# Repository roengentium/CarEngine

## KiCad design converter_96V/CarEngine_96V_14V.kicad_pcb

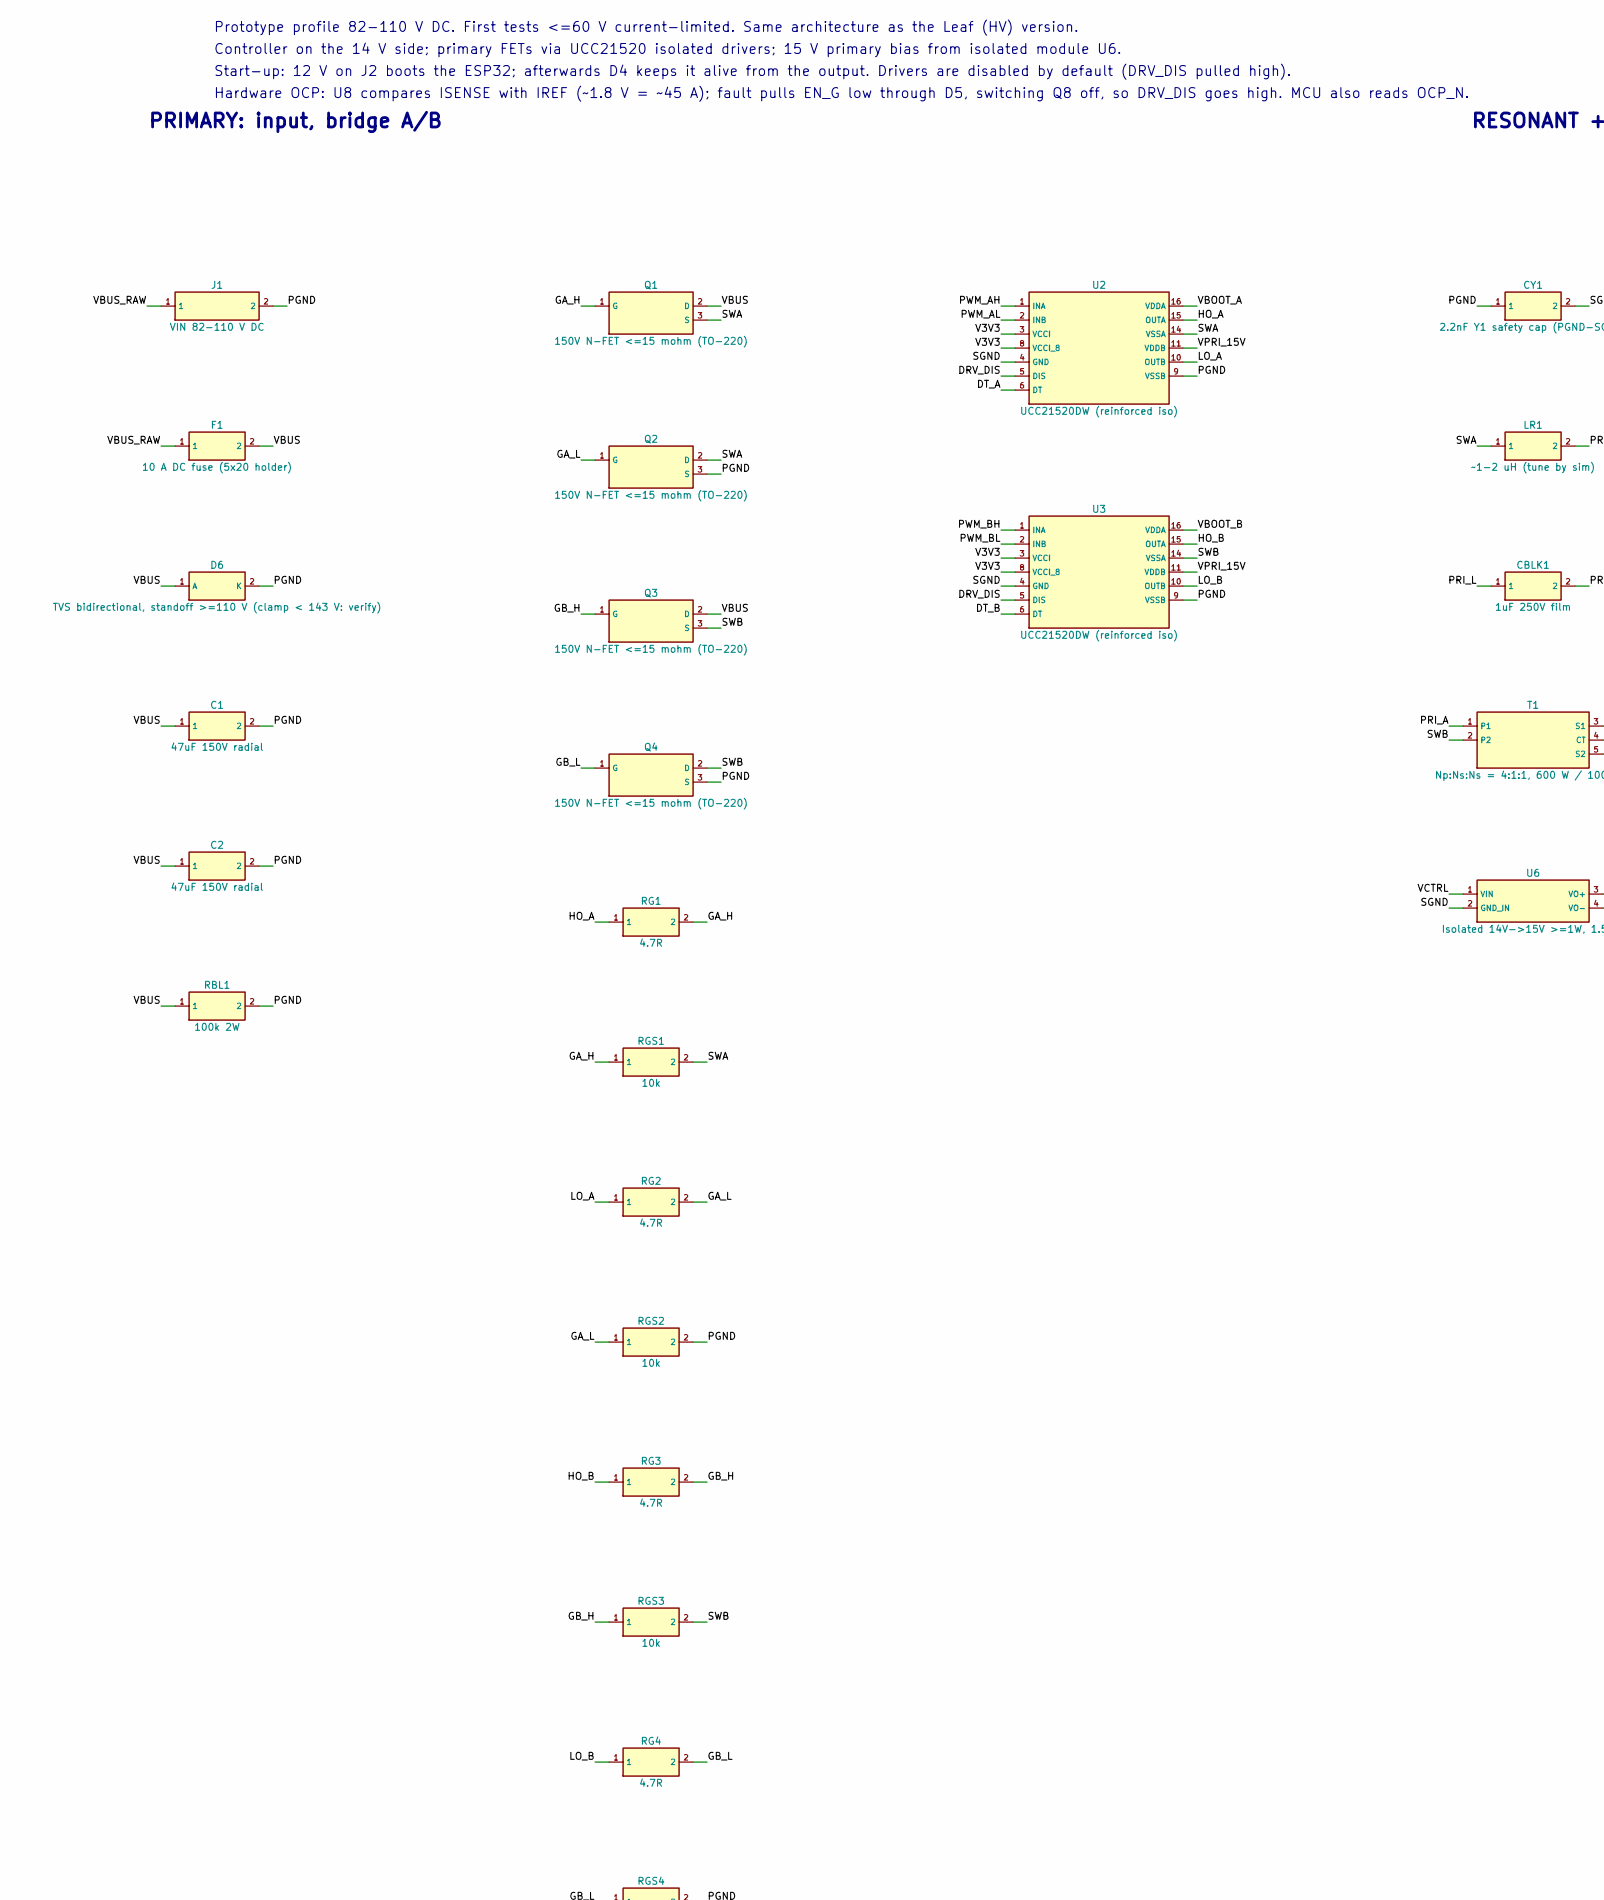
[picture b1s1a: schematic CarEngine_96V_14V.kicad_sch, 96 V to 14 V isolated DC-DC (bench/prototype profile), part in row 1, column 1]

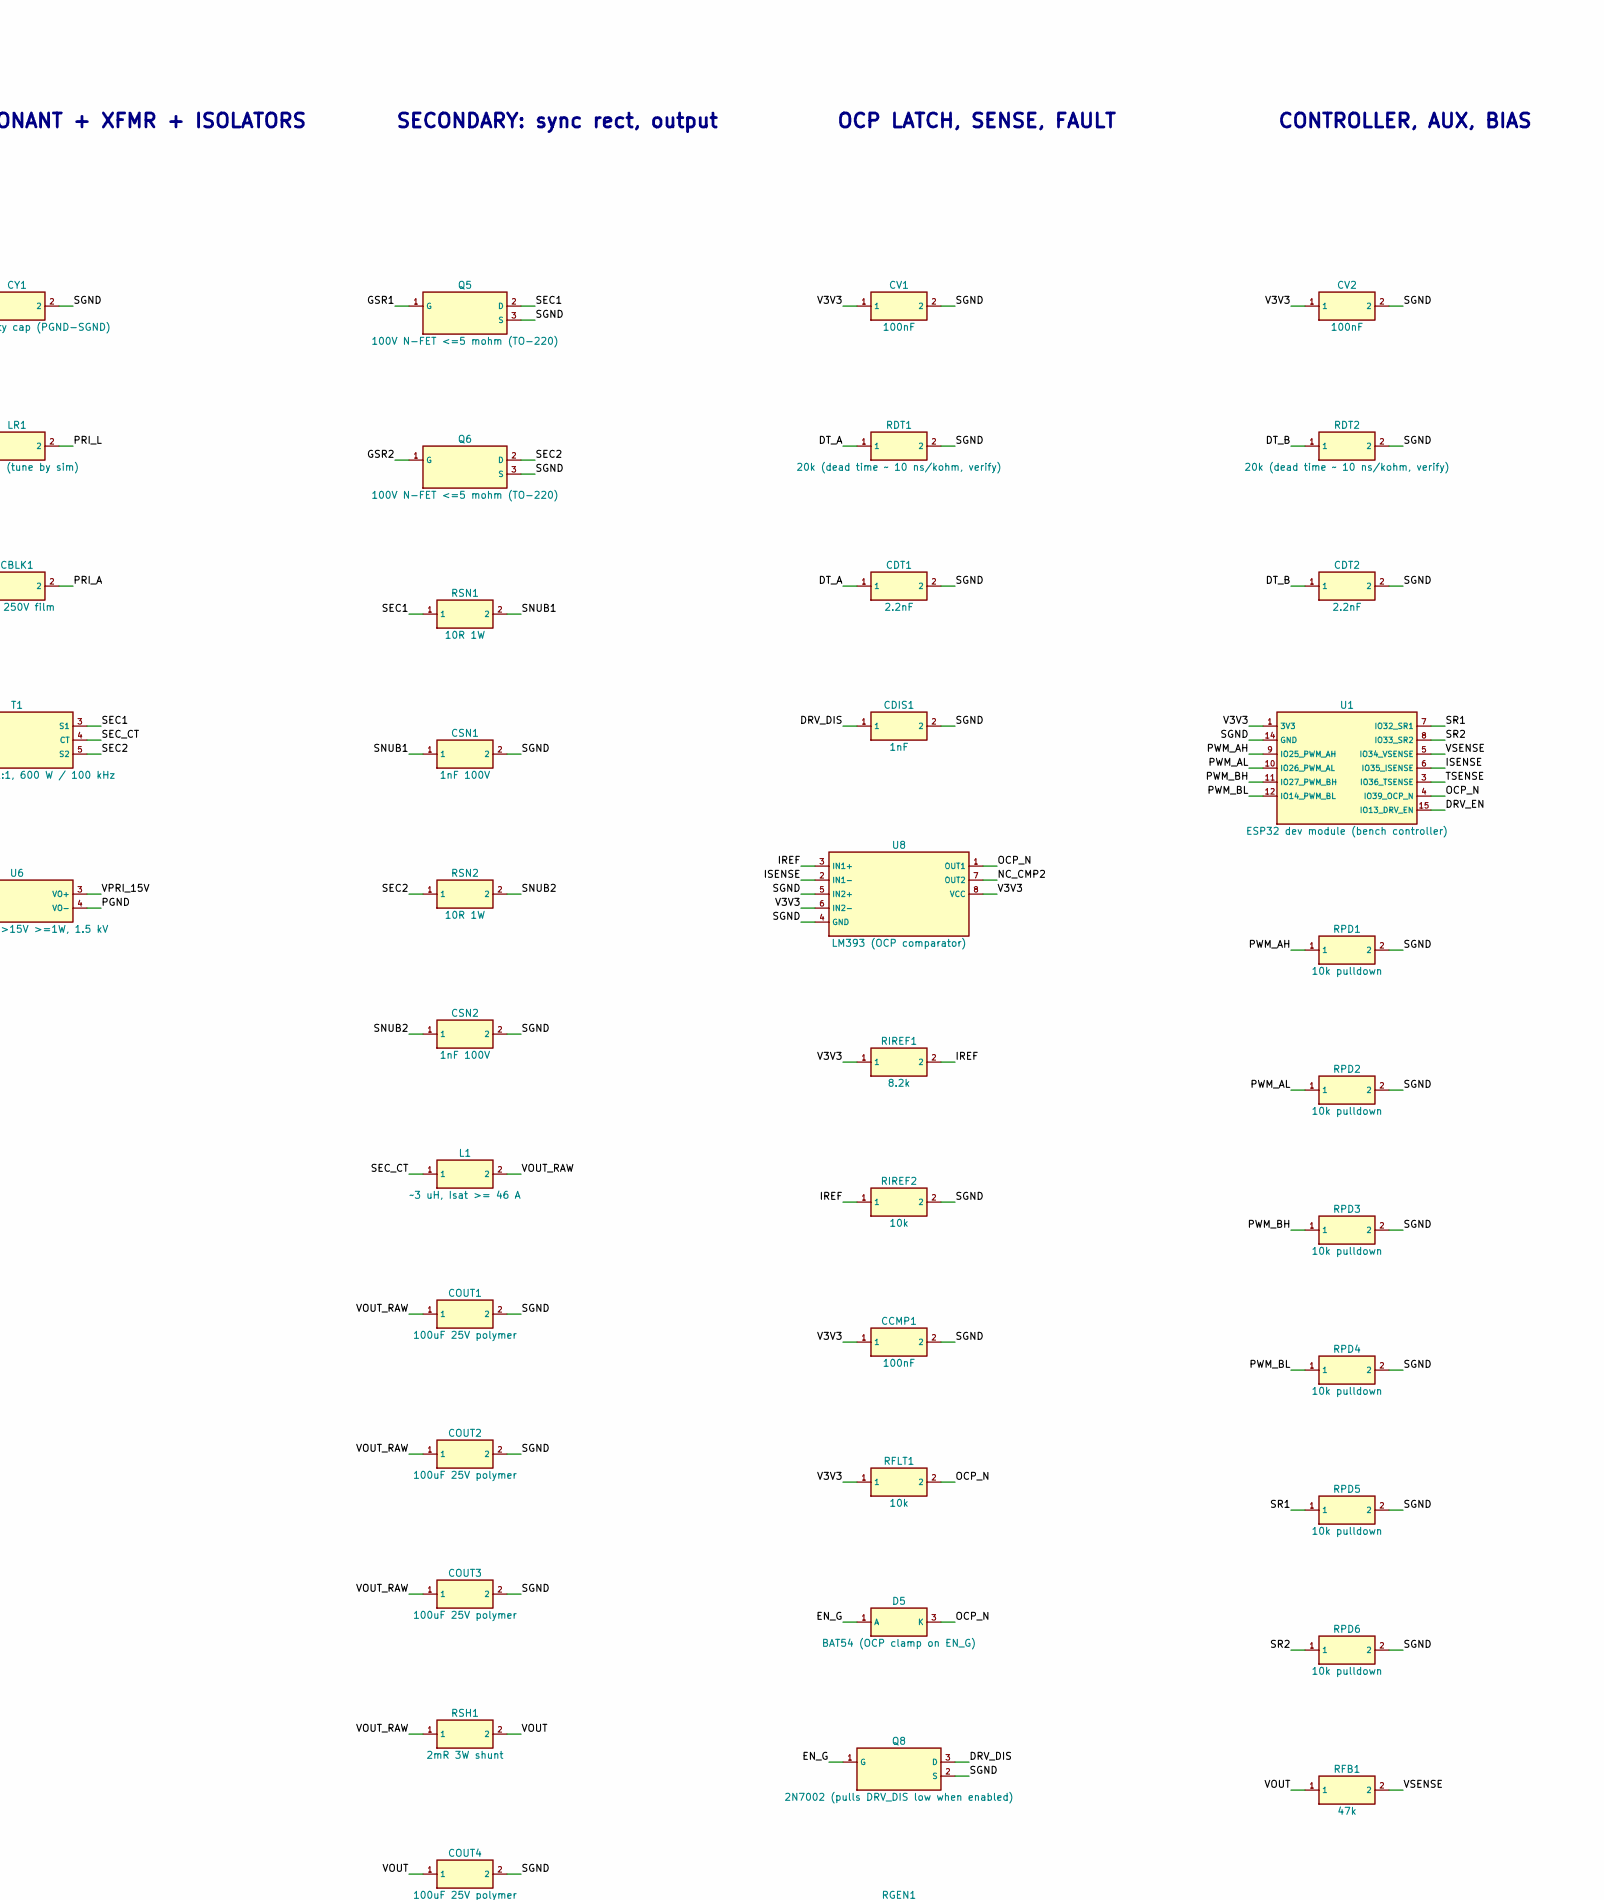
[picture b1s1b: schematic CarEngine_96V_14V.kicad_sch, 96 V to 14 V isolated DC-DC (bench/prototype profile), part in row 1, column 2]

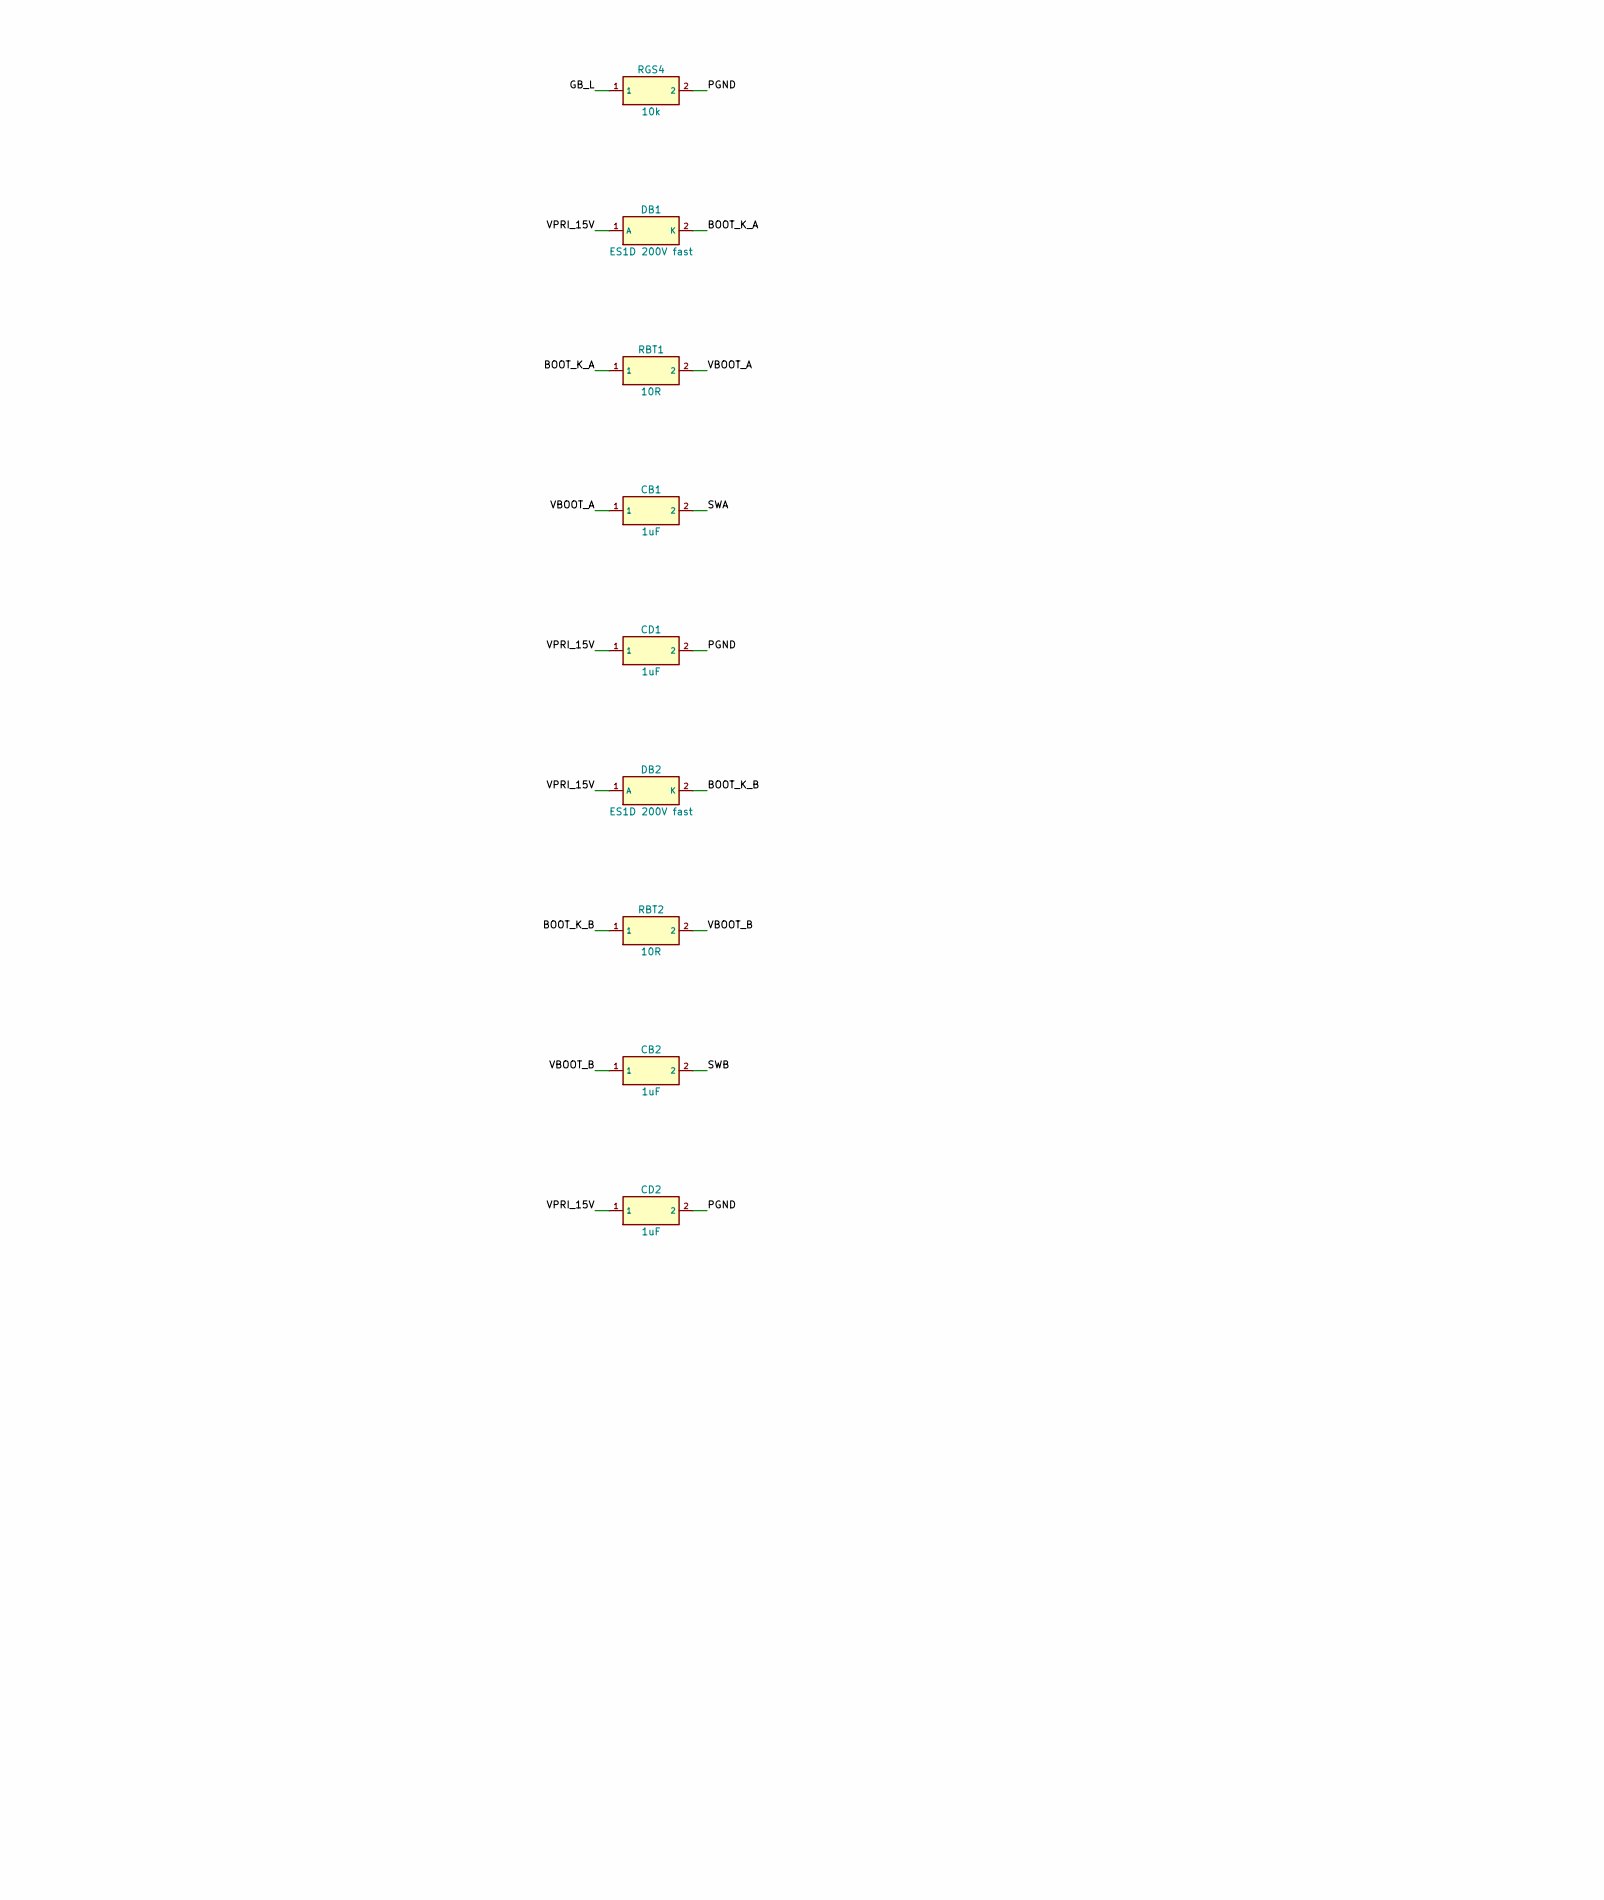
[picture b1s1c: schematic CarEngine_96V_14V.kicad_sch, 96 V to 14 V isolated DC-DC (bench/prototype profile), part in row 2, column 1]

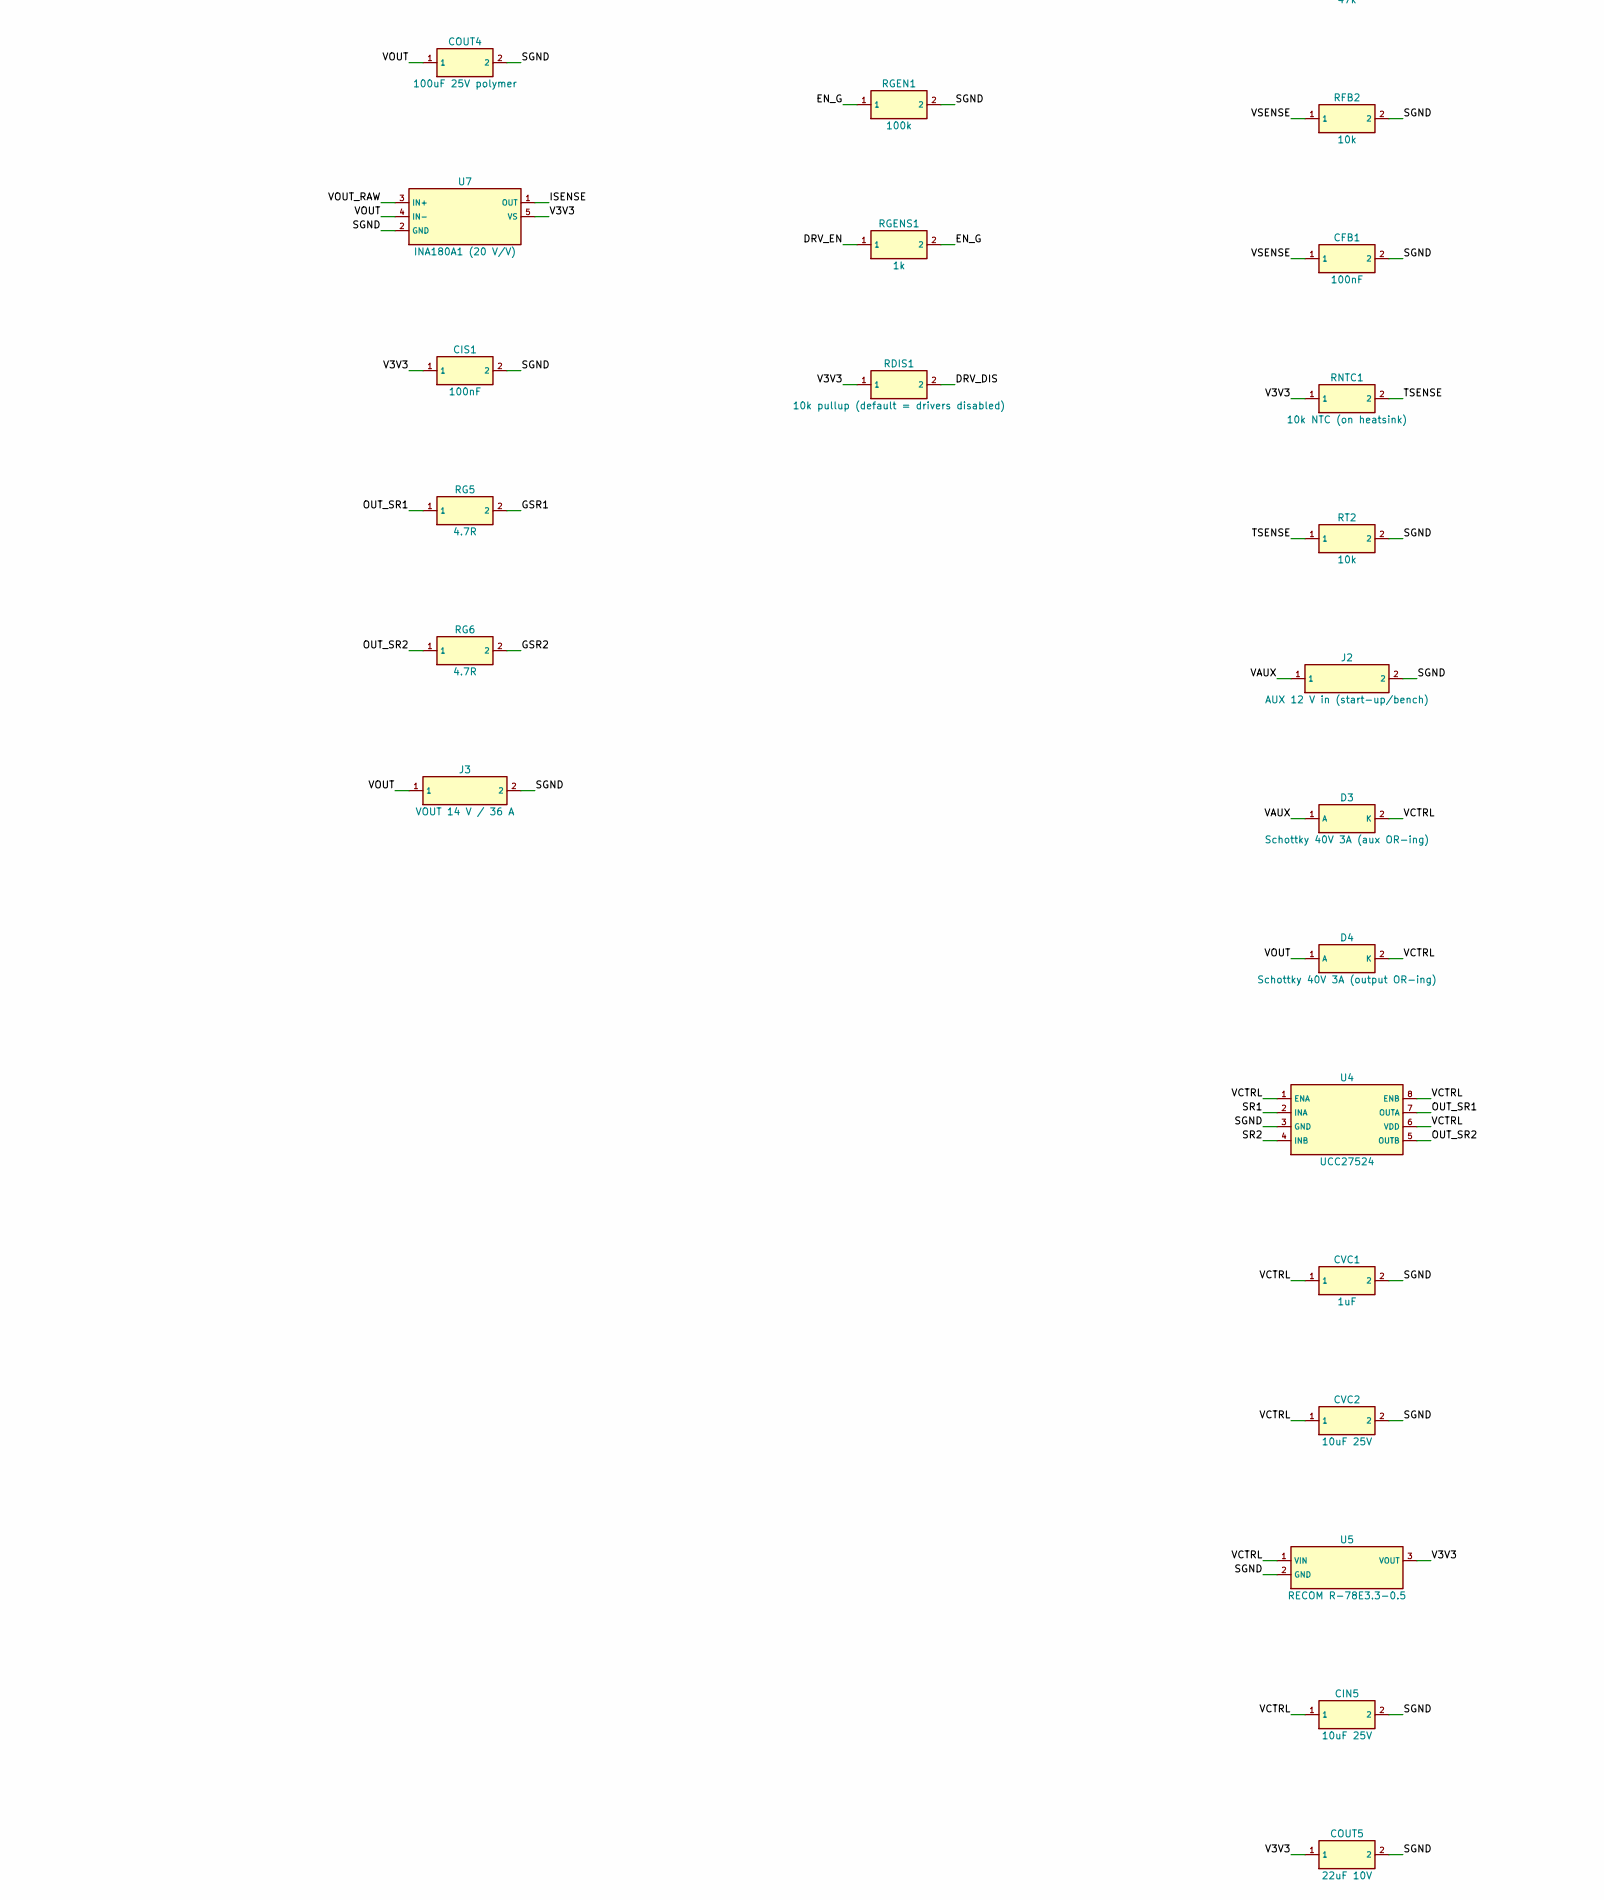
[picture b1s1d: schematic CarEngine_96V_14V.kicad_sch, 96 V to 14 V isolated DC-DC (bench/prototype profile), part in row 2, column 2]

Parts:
C1, C2: 47uF 150V radial; CAPR_P5.0
CB1, CB2: 1uF; R0805
CBLK1: 1uF 250V film; FILM_P10
CCMP1: 100nF; R0805
CD1, CD2: 1uF; R0805
CDIS1: 1nF; R0805
CDT1, CDT2: 2.2nF; R0805
CFB1: 100nF; R0805
CIN5: 10uF 25V; R0805
CIS1: 100nF; R0805
COUT1, COUT2, COUT3, COUT4: 100uF 25V polymer; CAPR_P3.5
COUT5: 22uF 10V; R0805
CSN1, CSN2: 1nF 100V; R0805
CV1, CV2: 100nF; R0805
CVC1: 1uF; R0805
CVC2: 10uF 25V; R0805
CY1: 2.2nF Y1 safety cap (PGND-SGND); YCAP_P7.5
D3: Schottky 40V 3A (aux OR-ing); SMC
D4: Schottky 40V 3A (output OR-ing); SMC
D5: BAT54 (OCP clamp on EN_G); SOT23
D6: TVS bidirectional, standoff >=110 V (clamp < 143 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; SMC
DB1, DB2: ES1D 200V fast; SMA
F1: 10 A DC fuse (5x20 holder); FUSE_P22.5
J1: VIN 82-110 V DC; TB2_P5.08
J2: AUX 12 V in (start-up/bench); TB2_P5.08
J3: VOUT 14 V / 36 A; TB2_P7.62_PWR
L1: ~3 uH, Isat >= 46 A; IND_PWR_P15
LR1: ~1-2 uH (tune by sim); IND_P10
Q1, Q2, Q3, Q4: 150V N-FET <=15 mohm (TO-220); TO220V
Q5, Q6: 100V N-FET <=5 mohm (TO-220); TO220V
Q8: 2N7002 (pulls DRV_DIS low when enabled); SOT23
RBL1: 100k 2W; RAX_P12.5
RBT1, RBT2: 10R; R0805
RDIS1: 10k pullup (default = drivers disabled); R0805
RDT1, RDT2: 20k (dead time ~ 10 ns/kohm, verify); R0805
RFB1: 47k; R0805
RFB2: 10k; R0805
RFLT1: 10k; R0805
RG1, RG2, RG3, RG4, RG5, RG6: 4.7R; R0805
RGEN1: 100k; R0805
RGENS1: 1k; R0805
RGS1, RGS2, RGS3, RGS4: 10k; R0805
RIREF1: 8.2k; R0805
RIREF2: 10k; R0805
RNTC1: 10k NTC (on heatsink); NTC_P5.08
RPD1, RPD2, RPD3, RPD4, RPD5, RPD6: 10k pulldown; R0805
RSH1: 2mR 3W shunt; R2512
RSN1, RSN2: 10R 1W; RPWR_P10
RT2: 10k; R0805
T1: Np:Ns:Ns = 4:1:1, 600 W / 100 kHz; XFMR_LV
U1: ESP32 dev module (bench controller); ESP32_DEVKIT38_R90
U2, U3: UCC21520DW (reinforced iso); SOIC16W_R180
U4: UCC27524; SOIC8
U5: RECOM R-78E3.3-0.5; SIP3_P2.54
U6: Isolated 14V->15V >=1W, 1.5 kV; ISO4_X7.62
U7: INA180A1 (20 V/V); SOT23_5
U8: LM393 (OCP comparator); SOIC8

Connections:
/BOOT_K_A: DB1.2 (K), RBT1.1
/BOOT_K_B: DB2.2 (K), RBT2.1
/DRV_DIS: CDIS1.1, Q8.3 (D), RDIS1.2, U2.5 (DIS), U3.5 (DIS)
/DRV_EN: RGENS1.1, U1.15 (IO13_DRV_EN)
/DT_A: CDT1.1, RDT1.1, U2.6 (DT)
/DT_B: CDT2.1, RDT2.1, U3.6 (DT)
/EN_G: D5.1 (A), Q8.1 (G), RGEN1.1, RGENS1.2
/GA_H: Q1.1 (G), RG1.2, RGS1.1
/GA_L: Q2.1 (G), RG2.2, RGS2.1
/GB_H: Q3.1 (G), RG3.2, RGS3.1
/GB_L: Q4.1 (G), RG4.2, RGS4.1
/GSR1: Q5.1 (G), RG5.2
/GSR2: Q6.1 (G), RG6.2
/HO_A: RG1.1, U2.15 (OUTA)
/HO_B: RG3.1, U3.15 (OUTA)
/IREF: RIREF1.2, RIREF2.1, U8.3 (IN1+)
/ISENSE: U1.6 (IO35_ISENSE), U7.1 (OUT), U8.2 (IN1-)
/LO_A: RG2.1, U2.10 (OUTB)
/LO_B: RG4.1, U3.10 (OUTB)
/NC_CMP2: U8.7 (OUT2)
/OCP_N: D5.3 (K), RFLT1.2, U1.4 (IO39_OCP_N), U8.1 (OUT1)
/OUT_SR1: RG5.1, U4.7 (OUTA)
/OUT_SR2: RG6.1, U4.5 (OUTB)
/PGND: C1.2, C2.2, CD1.2, CD2.2, CY1.1, D6.2 (K), J1.2, Q2.3 (S), Q4.3 (S), RBL1.2, RGS2.2, RGS4.2, U2.9 (VSSB), U3.9 (VSSB), U6.4 (VO-)
/PRI_A: CBLK1.2, T1.1
/PRI_L: CBLK1.1, LR1.2
/PWM_AH: RPD1.1, U1.9 (IO25_PWM_AH), U2.1 (INA)
/PWM_AL: RPD2.1, U1.10 (IO26_PWM_AL), U2.2 (INB)
/PWM_BH: RPD3.1, U1.11 (IO27_PWM_BH), U3.1 (INA)
/PWM_BL: RPD4.1, U1.12 (IO14_PWM_BL), U3.2 (INB)
/SEC1: Q5.2 (D), RSN1.1, T1.3 (S1)
/SEC2: Q6.2 (D), RSN2.1, T1.5 (S2)
/SEC_CT: L1.1, T1.4 (CT)
/SGND: CCMP1.2, CDIS1.2, CDT1.2, CDT2.2, CFB1.2, CIN5.2, CIS1.2, COUT1.2, COUT2.2, COUT3.2, COUT4.2, COUT5.2, CSN1.2, CSN2.2, CV1.2, CV2.2, CVC1.2, CVC2.2, CY1.2, J2.2, J3.2, Q5.3 (S), Q6.3 (S), Q8.2 (S), RDT1.2, RDT2.2, RFB2.2, RGEN1.2, RIREF2.2, RPD1.2, RPD2.2, RPD3.2, RPD4.2, RPD5.2, RPD6.2, RT2.2, U1.14 (GND), U2.4 (GND), U3.4 (GND), U4.3 (GND), U5.2 (GND), U6.2 (GND_IN), U7.2 (GND), U8.4 (GND), U8.5 (IN2+)
/SNUB1: CSN1.1, RSN1.2
/SNUB2: CSN2.1, RSN2.2
/SR1: RPD5.1, U1.7 (IO32_SR1), U4.2 (INA)
/SR2: RPD6.1, U1.8 (IO33_SR2), U4.4 (INB)
/SWA: CB1.2, LR1.1, Q1.3 (S), Q2.2 (D), RGS1.2, U2.14 (VSSA)
/SWB: CB2.2, Q3.3 (S), Q4.2 (D), RGS3.2, T1.2, U3.14 (VSSA)
/TSENSE: RNTC1.2, RT2.1, U1.3 (IO36_TSENSE)
/V3V3: CCMP1.1, CIS1.1, COUT5.1, CV1.1, CV2.1, RDIS1.1, RFLT1.1, RIREF1.1, RNTC1.1, U1.1 (3V3), U2.3 (VCCI), U2.8 (VCCI_8), U3.3 (VCCI), U3.8 (VCCI_8), U5.3 (VOUT), U7.5 (VS), U8.6 (IN2-), U8.8 (VCC)
/VAUX: D3.1 (A), J2.1
/VBOOT_A: CB1.1, RBT1.2, U2.16 (VDDA)
/VBOOT_B: CB2.1, RBT2.2, U3.16 (VDDA)
/VBUS: C1.1, C2.1, D6.1 (A), F1.2, Q1.2 (D), Q3.2 (D), RBL1.1
/VBUS_RAW: F1.1, J1.1
/VCTRL: CIN5.1, CVC1.1, CVC2.1, D3.2 (K), D4.2 (K), U4.1 (ENA), U4.6 (VDD), U4.8 (ENB), U5.1 (VIN), U6.1 (VIN)
/VOUT: COUT4.1, D4.1 (A), J3.1, RFB1.1, RSH1.2, U7.4 (IN-)
/VOUT_RAW: COUT1.1, COUT2.1, COUT3.1, L1.2, RSH1.1, U7.3 (IN+)
/VPRI_15V: CD1.1, CD2.1, DB1.1 (A), DB2.1 (A), U2.11 (VDDB), U3.11 (VDDB), U6.3 (VO+)
/VSENSE: CFB1.1, RFB1.2, RFB2.1, U1.5 (IO34_VSENSE)

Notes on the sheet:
PRIMARY: input, bridge A/B
RESONANT + XFMR + ISOLATORS
SECONDARY: sync rect, output
OCP LATCH, SENSE, FAULT
CONTROLLER, AUX, BIAS
Prototype profile 82-110 V DC. First tests <=60 V current-limited. Same architecture as the Leaf (HV) version.
Controller on the 14 V side; primary FETs via UCC21520 isolated drivers; 15 V primary bias from isolated module U6.
Start-up: 12 V on J2 boots the ESP32; afterwards D4 keeps it alive from the output. Drivers are disabled by default (DRV_DIS pulled high).
Hardware OCP: U8 compares ISENSE with IREF (~1.8 V = ~45 A); fault pulls EN_G low through D5, switching Q8 off, so DRV_DIS goes high. MCU also reads OCP_N.

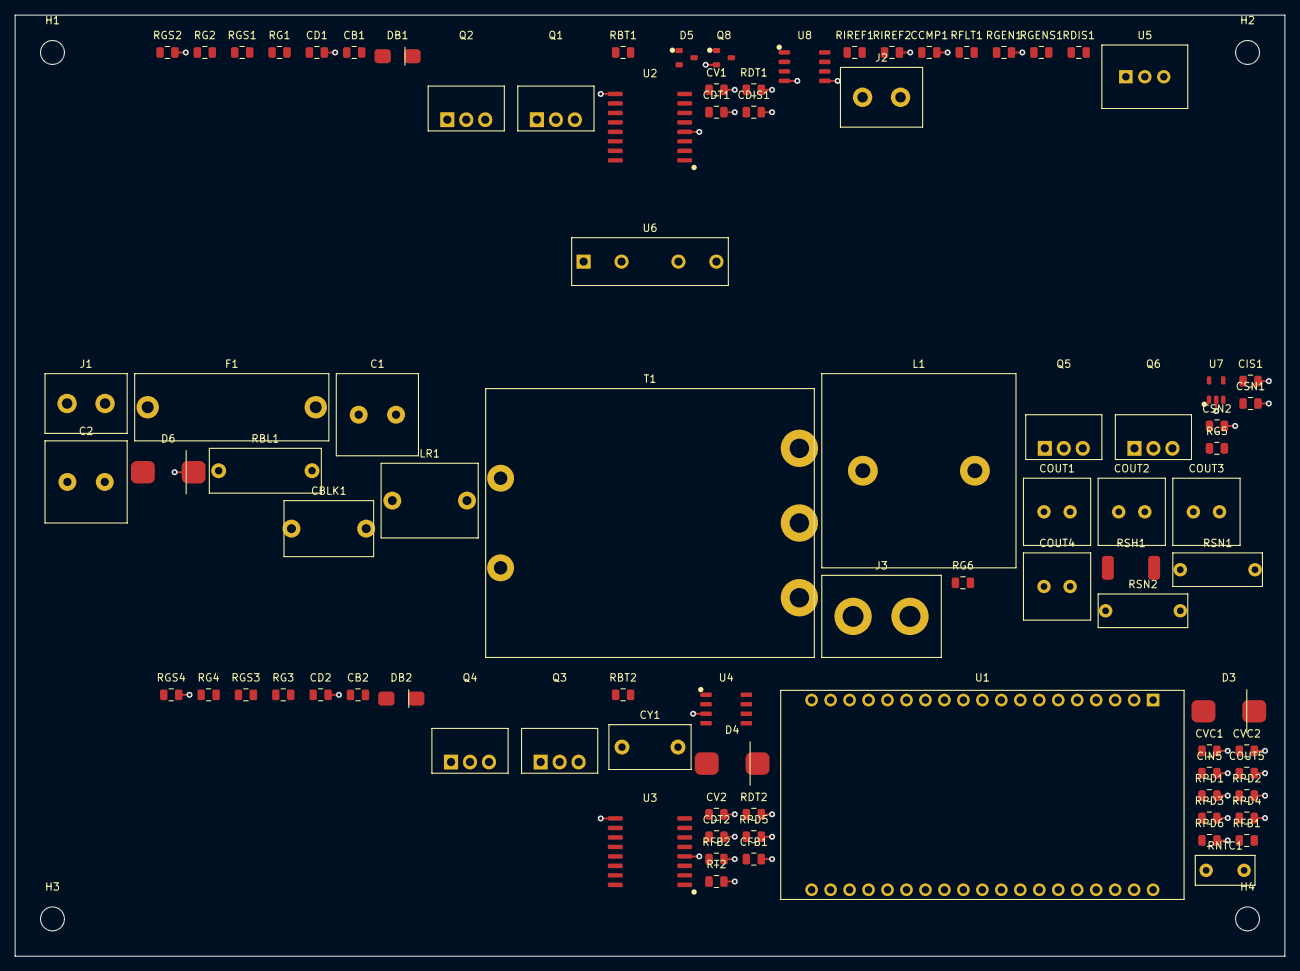
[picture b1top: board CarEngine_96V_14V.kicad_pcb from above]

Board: 2 copper layers, 170.0 x 126.0 mm, 92 parts (0 on the bottom side), 51 nets.

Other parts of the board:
H1, H2, H3, H4: M3; MountingHole_M3

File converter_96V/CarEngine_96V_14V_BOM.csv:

Ref,Value,Footprint,Qty-note
C1,47uF 150V radial,CarEngineGen:CAPR_P5.0,
C2,47uF 150V radial,CarEngineGen:CAPR_P5.0,
CB1,1uF,CarEngineGen:R0805,
CB2,1uF,CarEngineGen:R0805,
CBLK1,1uF 250V film,CarEngineGen:FILM_P10,
CCMP1,100nF,CarEngineGen:R0805,
CD1,1uF,CarEngineGen:R0805,
CD2,1uF,CarEngineGen:R0805,
CDIS1,1nF,CarEngineGen:R0805,
CDT1,2.2nF,CarEngineGen:R0805,
CDT2,2.2nF,CarEngineGen:R0805,
CFB1,100nF,CarEngineGen:R0805,
CIN5,10uF 25V,CarEngineGen:R0805,
CIS1,100nF,CarEngineGen:R0805,
COUT1,100uF 25V polymer,CarEngineGen:CAPR_P3.5,
COUT2,100uF 25V polymer,CarEngineGen:CAPR_P3.5,
COUT3,100uF 25V polymer,CarEngineGen:CAPR_P3.5,
COUT4,100uF 25V polymer,CarEngineGen:CAPR_P3.5,
COUT5,22uF 10V,CarEngineGen:R0805,
CSN1,1nF 100V,CarEngineGen:R0805,
CSN2,1nF 100V,CarEngineGen:R0805,
CV1,100nF,CarEngineGen:R0805,
CV2,100nF,CarEngineGen:R0805,
CVC1,1uF,CarEngineGen:R0805,
CVC2,10uF 25V,CarEngineGen:R0805,
CY1,2.2nF Y1 safety cap (PGND-SGND),CarEngineGen:YCAP_P7.5,
D3,Schottky 40V 3A (aux OR-ing),CarEngineGen:SMC,
D4,Schottky 40V 3A (output OR-ing),CarEngineGen:SMC,
D5,BAT54 (OCP clamp on EN_G),CarEngineGen:SOT23,
D6,"TVS bidirectional, standoff >=110 V (clamp < 143 V: verify)",CarEngineGen:SMC,
DB1,ES1D 200V fast,CarEngineGen:SMA,
DB2,ES1D 200V fast,CarEngineGen:SMA,
F1,10 A DC fuse (5x20 holder),CarEngineGen:FUSE_P22.5,
J1,VIN 82-110 V DC,CarEngineGen:TB2_P5.08,
J2,AUX 12 V in (start-up/bench),CarEngineGen:TB2_P5.08,
J3,VOUT 14 V / 36 A,CarEngineGen:TB2_P7.62_PWR,
L1,"~3 uH, Isat >= 46 A",CarEngineGen:IND_PWR_P15,
LR1,~1-2 uH (tune by sim),CarEngineGen:IND_P10,
Q1,150V N-FET <=15 mohm (TO-220),CarEngineGen:TO220V,
Q2,150V N-FET <=15 mohm (TO-220),CarEngineGen:TO220V,
Q3,150V N-FET <=15 mohm (TO-220),CarEngineGen:TO220V,
Q4,150V N-FET <=15 mohm (TO-220),CarEngineGen:TO220V,
Q5,100V N-FET <=5 mohm (TO-220),CarEngineGen:TO220V,
Q6,100V N-FET <=5 mohm (TO-220),CarEngineGen:TO220V,
Q8,2N7002 (pulls DRV_DIS low when enabled),CarEngineGen:SOT23,
RBL1,100k 2W,CarEngineGen:RAX_P12.5,
RBT1,10R,CarEngineGen:R0805,
RBT2,10R,CarEngineGen:R0805,
RDIS1,10k pullup (default = drivers disabled),CarEngineGen:R0805,
RDT1,"20k (dead time ~ 10 ns/kohm, verify)",CarEngineGen:R0805,
RDT2,"20k (dead time ~ 10 ns/kohm, verify)",CarEngineGen:R0805,
RFB1,47k,CarEngineGen:R0805,
RFB2,10k,CarEngineGen:R0805,
RFLT1,10k,CarEngineGen:R0805,
RG1,4.7R,CarEngineGen:R0805,
RG2,4.7R,CarEngineGen:R0805,
RG3,4.7R,CarEngineGen:R0805,
RG4,4.7R,CarEngineGen:R0805,
RG5,4.7R,CarEngineGen:R0805,
RG6,4.7R,CarEngineGen:R0805,
RGEN1,100k,CarEngineGen:R0805,
RGENS1,1k,CarEngineGen:R0805,
RGS1,10k,CarEngineGen:R0805,
RGS2,10k,CarEngineGen:R0805,
RGS3,10k,CarEngineGen:R0805,
RGS4,10k,CarEngineGen:R0805,
RIREF1,8.2k,CarEngineGen:R0805,
RIREF2,10k,CarEngineGen:R0805,
RNTC1,10k NTC (on heatsink),CarEngineGen:NTC_P5.08,
RPD1,10k pulldown,CarEngineGen:R0805,
RPD2,10k pulldown,CarEngineGen:R0805,
RPD3,10k pulldown,CarEngineGen:R0805,
RPD4,10k pulldown,CarEngineGen:R0805,
RPD5,10k pulldown,CarEngineGen:R0805,
RPD6,10k pulldown,CarEngineGen:R0805,
RSH1,2mR 3W shunt,CarEngineGen:R2512,
RSN1,10R 1W,CarEngineGen:RPWR_P10,
RSN2,10R 1W,CarEngineGen:RPWR_P10,
RT2,10k,CarEngineGen:R0805,
T1,"Np:Ns:Ns = 4:1:1, 600 W / 100 kHz",CarEngineGen:XFMR_LV,
U1,ESP32 dev module (bench controller),CarEngineGen:ESP32_DEVKIT38_R90,
U2,UCC21520DW (reinforced iso),CarEngineGen:SOIC16W_R180,
U3,UCC21520DW (reinforced iso),CarEngineGen:SOIC16W_R180,
U4,UCC27524,CarEngineGen:SOIC8,
U5,RECOM R-78E3.3-0.5,CarEngineGen:SIP3_P2.54,
U6,"Isolated 14V->15V >=1W, 1.5 kV",CarEngineGen:ISO4_X7.62,
U7,INA180A1 (20 V/V),CarEngineGen:SOT23_5,
U8,LM393 (OCP comparator),CarEngineGen:SOIC8,

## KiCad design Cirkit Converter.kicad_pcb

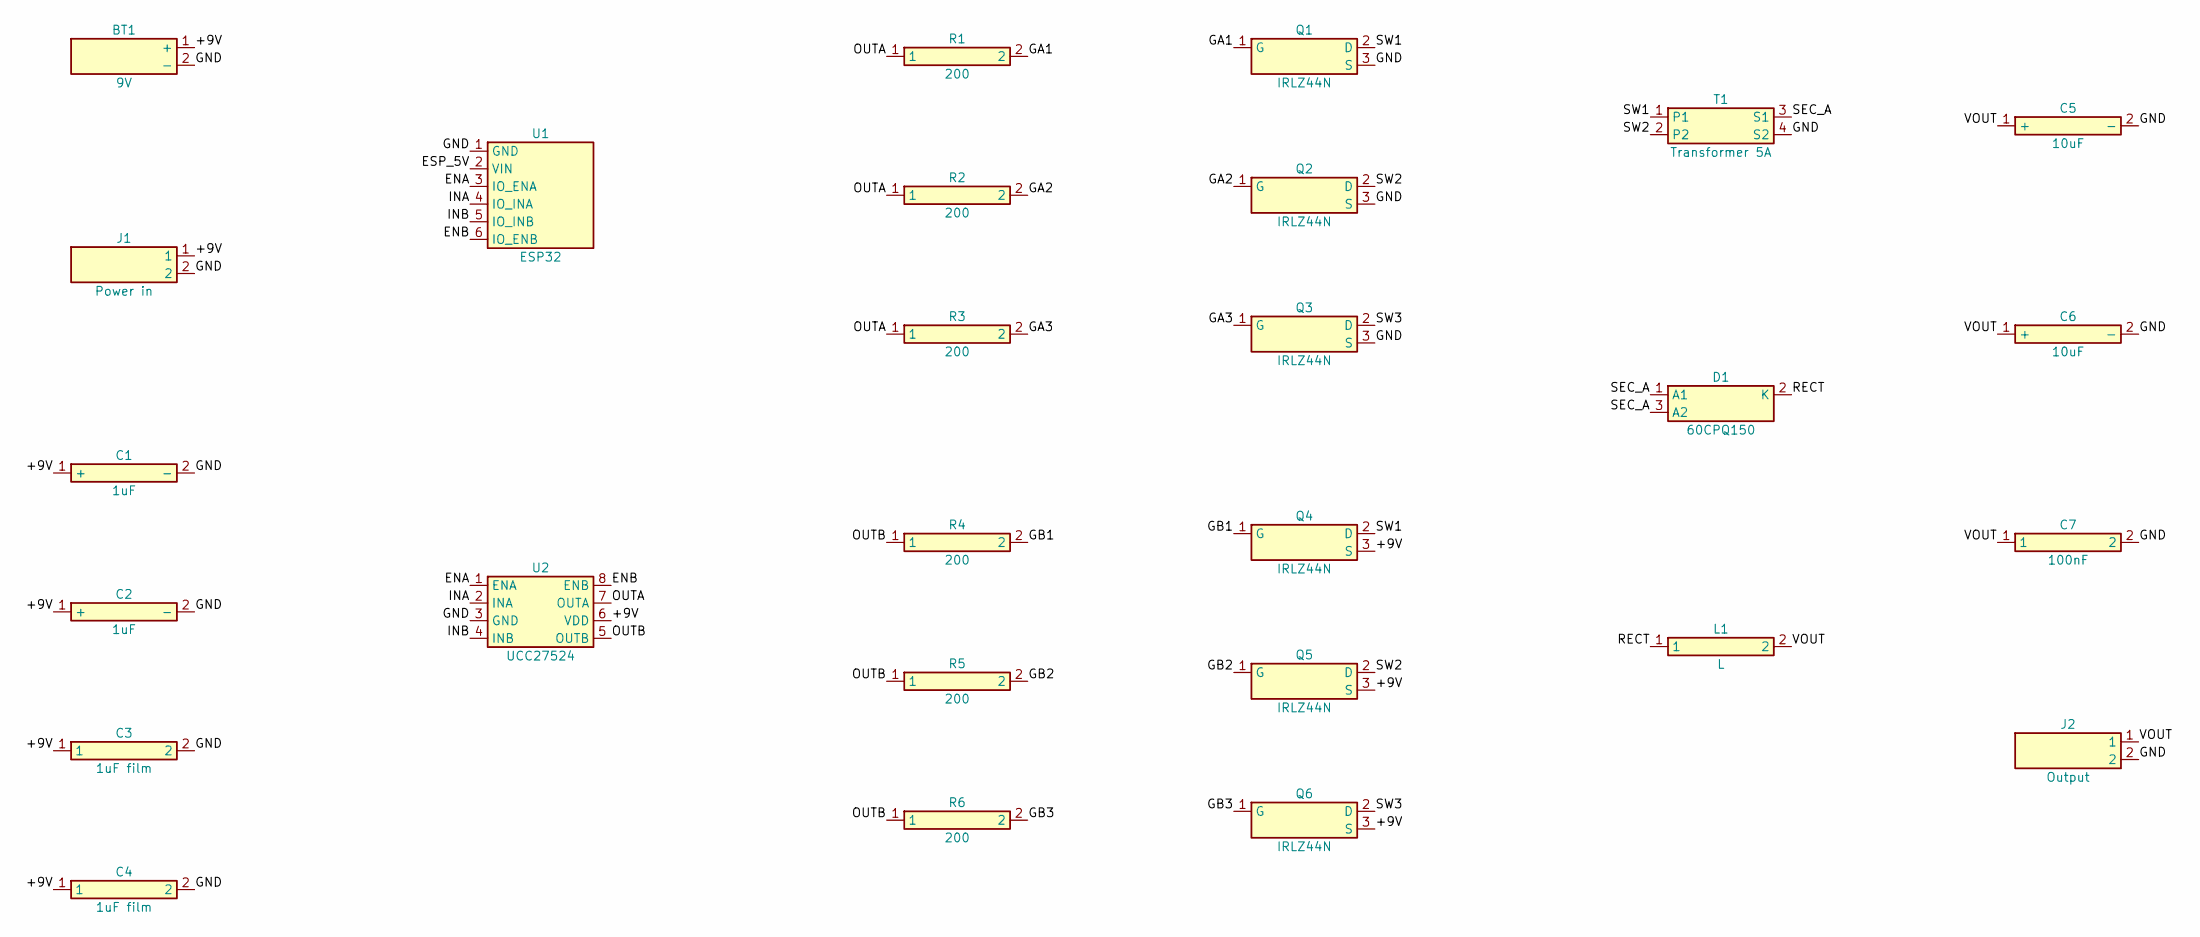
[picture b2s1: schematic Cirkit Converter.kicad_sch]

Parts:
BT1: 9V; TerminalBlock_2P_5.08mm
C1, C2: 1uF; C_Radial_P2.50mm
C3, C4: 1uF film; C_Rect_P7.50mm
C5, C6: 10uF; C_Radial_P2.50mm
C7: 100nF; C_Disc_P5.00mm
D1: 60CPQ150; TO-247-3_Vertical
J1: Power in; TerminalBlock_2P_5.08mm
J2: Output; TerminalBlock_2P_5.08mm
L1: L; L_Axial_P12.70mm
Q1, Q2, Q3, Q4, Q5, Q6: IRLZ44N; TO-220-3_Vertical
R1, R2, R3, R4, R5, R6: 200; R_Axial_P10.16mm
T1: Transformer 5A; Transformer_2x2_P5.08x10.16mm
U1: ESP32; PinHeader_1x06_P2.54mm
U2: UCC27524; SOIC-8_3.9x4.9mm_P1.27mm

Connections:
+9V: BT1.1 (+), C1.1 (+), C2.1 (+), C3.1, C4.1, J1.1, Q4.3 (S), Q5.3 (S), Q6.3 (S), U2.6 (VDD)
ENA: U1.3 (IO_ENA), U2.1 (ENA)
ENB: U1.6 (IO_ENB), U2.8 (ENB)
ESP_5V: U1.2 (VIN)
GA1: Q1.1 (G), R1.2
GA2: Q2.1 (G), R2.2
GA3: Q3.1 (G), R3.2
GB1: Q4.1 (G), R4.2
GB2: Q5.1 (G), R5.2
GB3: Q6.1 (G), R6.2
GND: BT1.2 (-), C1.2 (-), C2.2 (-), C3.2, C4.2, C5.2 (-), C6.2 (-), C7.2, J1.2, J2.2, Q1.3 (S), Q2.3 (S), Q3.3 (S), T1.4 (S2), U1.1 (GND), U2.3 (GND)
INA: U1.4 (IO_INA), U2.2 (INA)
INB: U1.5 (IO_INB), U2.4 (INB)
OUTA: R1.1, R2.1, R3.1, U2.7 (OUTA)
OUTB: R4.1, R5.1, R6.1, U2.5 (OUTB)
RECT: D1.2 (K), L1.1
SEC_A: D1.1 (A1), D1.3 (A2), T1.3 (S1)
SW1: Q1.2 (D), Q4.2 (D), T1.1
SW2: Q2.2 (D), Q5.2 (D), T1.2
SW3: Q3.2 (D), Q6.2 (D)
VOUT: C5.1 (+), C6.1 (+), C7.1, J2.1, L1.2

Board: 2 copper layers, 27 parts (0 on the bottom side), 20 nets, no tracks yet.
